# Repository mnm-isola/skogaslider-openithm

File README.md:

# WIP DO NOT USE

Skogaslider PCB designed as a drop in replacement for existing Openithm controller

With a RP2040-Zero, 3 MPR121 breakout modules and a 74HC4051 breakout module

Should have compatibility with analog air towers and digital air towers.

6 pots for adjusting photodiodes instead of trying through different resistor values.

[skogaslider](https://github.com/skogaby/skogaslider)

Note: RPi Pico is too long to fit

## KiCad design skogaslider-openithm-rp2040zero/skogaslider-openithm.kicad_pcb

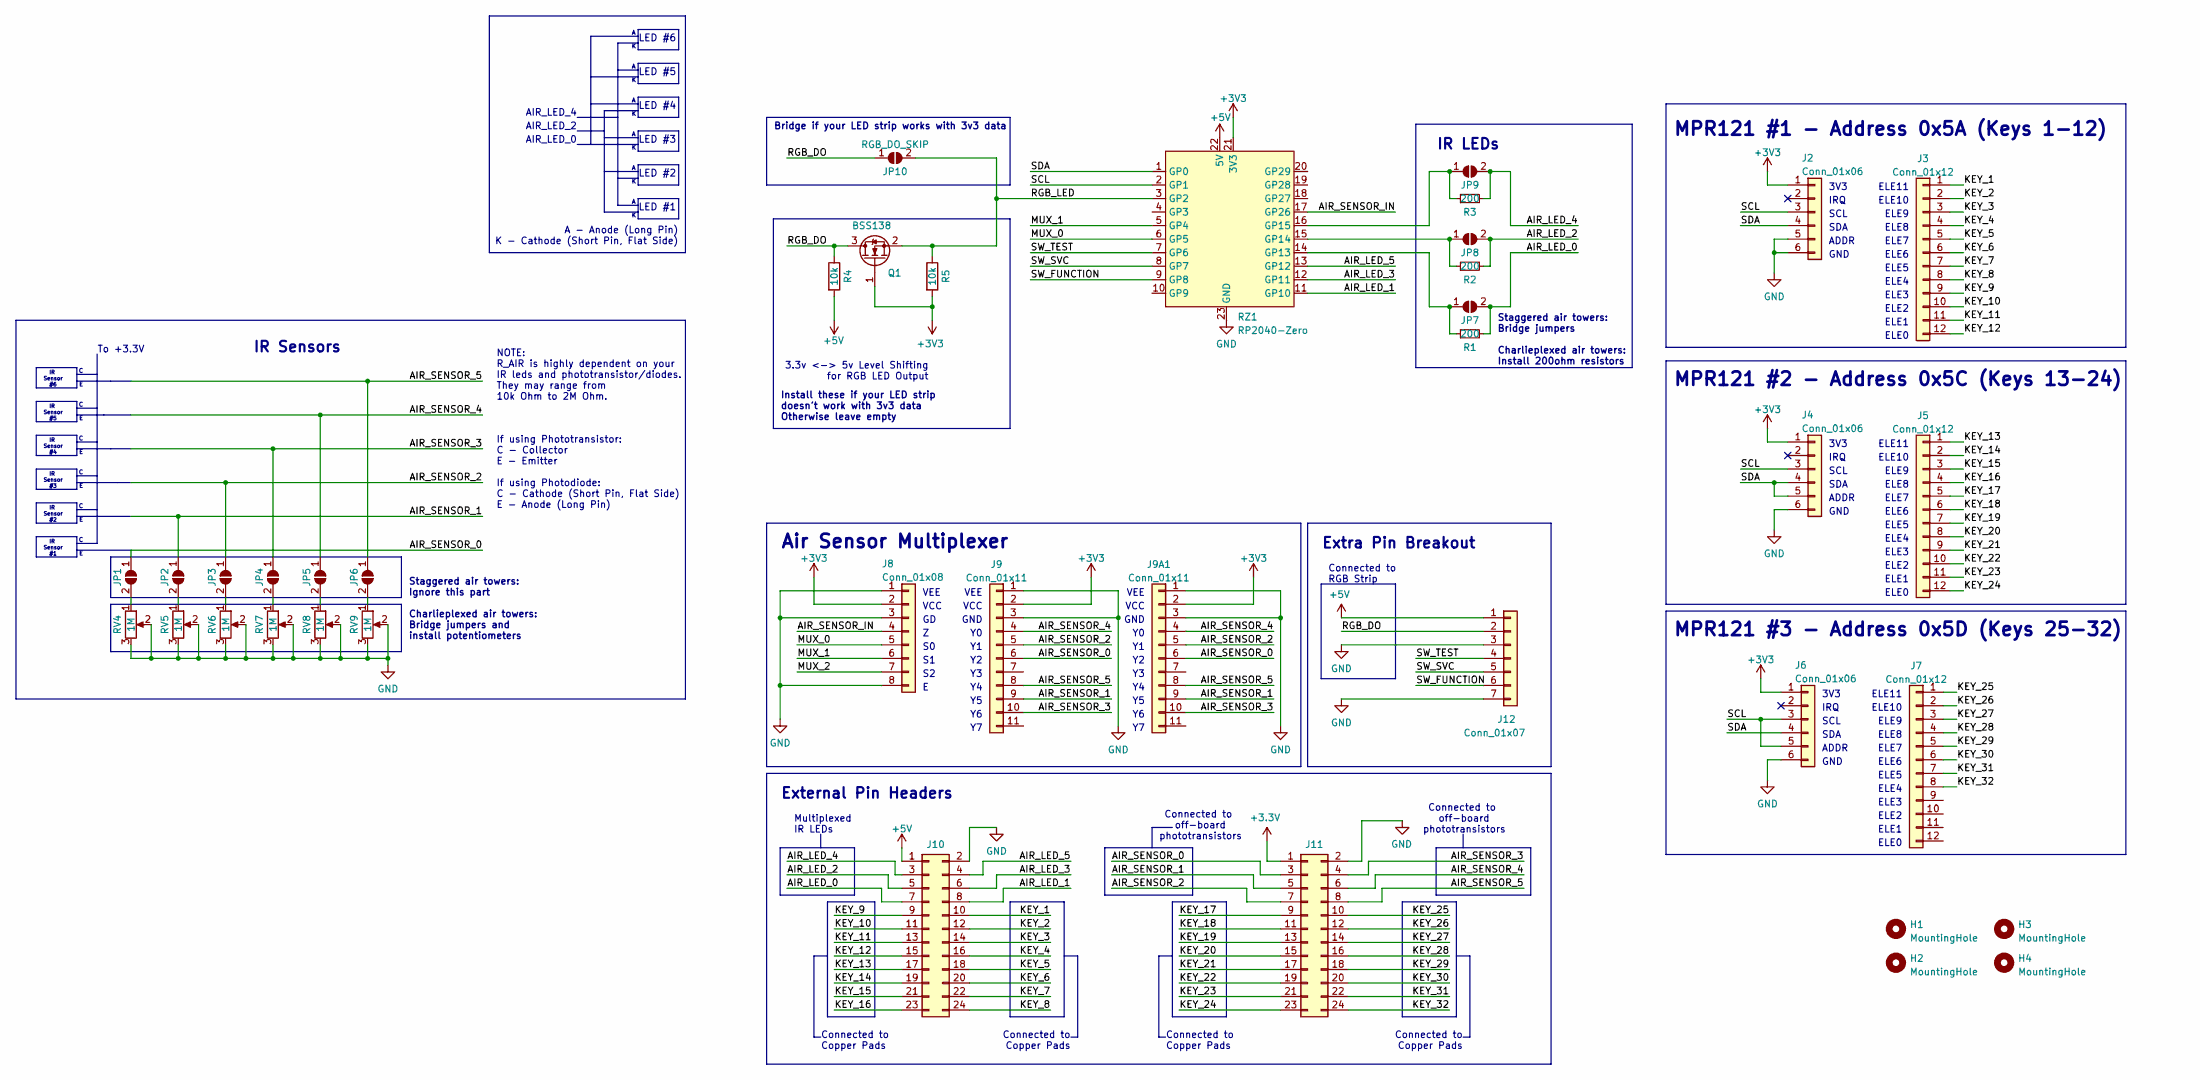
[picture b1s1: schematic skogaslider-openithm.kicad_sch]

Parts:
H1, H2, H3, H4: MountingHole; MountingHole_3.2mm_M3
J2, J4, J6: Conn_01x06; PinSocket_1x06_P2.54mm_Vertical
J3, J5, J7: Conn_01x12; PinSocket_1x12_P2.54mm_Vertical
J8: Conn_01x08; PinSocket_1x08_P2.54mm_Vertical
J9, J9A1: Conn_01x11; PinSocket_1x11_P2.54mm_Vertical
J10, J11: Conn_02x12_Odd_Even; PinHeader_2x12_P2.54mm_Horizontal
J12: Conn_01x07; PinHeader_1x07_P2.54mm_Vertical
JP1, JP2, JP3, JP4, JP5, JP6: AIR_MPLEX_JUMPER; SolderJumper-2_P1.3mm_Open_RoundedPad1.0x1.5mm
JP7, JP8, JP9: IR_STAG_JUMPER; SolderJumper-2_P1.3mm_Open_RoundedPad1.0x1.5mm
JP10: RGB_DO_SKIP; SolderJumper-2_P1.3mm_Open_RoundedPad1.0x1.5mm
Q1: BSS138; SOT-23
R1, R2, R3: 200; R_Axial_DIN0204_L3.6mm_D1.6mm_P5.08mm_Horizontal
R4, R5: 10k; R_0805_2012Metric_Pad1.20x1.40mm_HandSolder
RV4, RV5, RV6, RV7, RV8, RV9: 1M; Potentiometer_Runtron_RM-065_Vertical
RZ1: RP2040-Zero

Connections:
+5V: J10.1, J12.1, R4.2, RZ1.22 (5V)
/AIR_LED_0: J10.7, JP7.2 (B), R1.2
/AIR_LED_1: J10.8, RZ1.11 (GP10)
/AIR_LED_2: J10.5, JP8.2 (B), R2.2
/AIR_LED_3: J10.6, RZ1.12 (GP11)
/AIR_LED_4: J10.3, JP9.2 (B), R3.2
/AIR_LED_5: J10.4, RZ1.13 (GP12)
/AIR_SENSOR_0: J9.6, J9A1.6, J11.3, JP1.1 (A)
/AIR_SENSOR_1: J9.9, J9A1.9, J11.5, JP2.1 (A)
/AIR_SENSOR_2: J9.5, J9A1.5, J11.7, JP3.1 (A)
/AIR_SENSOR_3: J9.10, J9A1.10, J11.4, JP4.1 (A)
/AIR_SENSOR_4: J9.4, J9A1.4, J11.6, JP5.1 (A)
/AIR_SENSOR_5: J9.8, J9A1.8, J11.8, JP6.1 (A)
/AIR_SENSOR_IN: J8.4, RZ1.17 (GP26)
/KEY_1: J3.1, J10.10
/KEY_2: J3.2, J10.12
/KEY_3: J3.3, J10.14
/KEY_4: J3.4, J10.16
/KEY_5: J3.5, J10.18
/KEY_6: J3.6, J10.20
/KEY_7: J3.7, J10.22
/KEY_8: J3.8, J10.24
/KEY_9: J3.9, J10.9
/KEY_10: J3.10, J10.11
/KEY_11: J3.11, J10.13
/KEY_12: J3.12, J10.15
/KEY_13: J5.1, J10.17
/KEY_14: J5.2, J10.19
/KEY_15: J5.3, J10.21
/KEY_16: J5.4, J10.23
/KEY_17: J5.5, J11.9
/KEY_18: J5.6, J11.11
/KEY_19: J5.7, J11.13
/KEY_20: J5.8, J11.15
/KEY_21: J5.9, J11.17
/KEY_22: J5.10, J11.19
/KEY_23: J5.11, J11.21
/KEY_24: J5.12, J11.23
/KEY_25: J7.1, J11.10
/KEY_26: J7.2, J11.12
/KEY_27: J7.3, J11.14
/KEY_28: J7.4, J11.16
/KEY_29: J7.5, J11.18
/KEY_30: J7.6, J11.20
/KEY_31: J7.7, J11.22
/KEY_32: J7.8, J11.24
/MUX_0: J8.5, RZ1.6 (GP5)
/MUX_1: J8.6, RZ1.5 (GP4)
/MUX_2: J8.7
/RGB_DO: J12.2, JP10.1 (A), Q1.3 (D), R4.1
/RGB_LED: JP10.2 (B), Q1.2 (S), R5.1, RZ1.3 (GP2)
/SCL: J2.3, J4.3, J6.3, J6.5, RZ1.2 (GP1)
/SDA: J2.4, J4.4, J4.5, J6.4, RZ1.1 (GP0)
/SW_FUNCTION: J12.6, RZ1.9 (GP8)
/SW_SVC: J12.5, RZ1.8 (GP7)
/SW_TEST: J12.4, RZ1.7 (GP6)
GND: J2.5, J2.6, J4.6, J6.6, J8.1, J8.3, J8.8, J9.1, J9.3, J9A1.1, J9A1.3, J10.2, J11.2, J12.3, J12.7, RV4.2, RV4.3, RV5.2, RV5.3, RV6.2, RV6.3, RV7.2, RV7.3, RV8.2, RV8.3, RV9.2, RV9.3, RZ1.23 (GND)
unnamed: JP1.2 (B), RV4.1
unnamed: JP2.2 (B), RV5.1
unnamed: JP3.2 (B), RV6.1
unnamed: JP4.2 (B), RV7.1
unnamed: JP5.2 (B), RV8.1
unnamed: JP6.2 (B), RV9.1
unnamed: JP7.1 (A), R1.1, RZ1.14 (GP13)
unnamed: JP8.1 (A), R2.1, RZ1.15 (GP14)
unnamed: JP9.1 (A), R3.1, RZ1.16 (GP15)

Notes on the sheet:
ELE4
IRQ
VEE
ELE10
LED #5
SDA
3.3v <-> 5v Level Shifting for RGB LED Output
IR Sensors
ELE3
IR Sensor #5
IR LEDs
IR Sensor #3
ELE2
LED #2
Install these if your LED strip doesn't work with 3v3 data Otherwise leave empty
ELE1
ELE9
MPR121 #1 - Address 0x5A (Keys 1-12)
MPR121 #2 - Address 0x5C (Keys 13-24)
ADDR
LED #4
Connected to Copper Pads
SCL
GND
ELE6
Staggered air towers: Bridge jumpers Charlieplexed air towers: Install 200ohm resistors
Extra Pin Breakout
VCC
ELE8
ELE0
GND
Connected to off-board phototransistors
A - Anode (Long Pin) K - Cathode (Short Pin, Flat Side)
Connected to RGB Strip
IR Sensor #2
If using Phototransistor: C - Collector E - Emitter If using Photodiode: C - Cathode (Short Pin, Flat Side) E - Anode (Long Pin)
ELE5
To +3.3V
IR Sensor #6
MPR121 #3 - Address 0x5D (Keys 25-32)

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
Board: 2 copper layers, 39 parts (13 on the bottom side), 66 nets, no tracks yet.
